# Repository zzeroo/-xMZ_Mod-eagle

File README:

# xMZ-Mod-Touch Eagle Files

Eagle files for the 'xMZ-Mod-Touch' project.

# Material Listen (BOM)

Die Material Listen werden aus den Eagle Zeichnungen gewonnen. Hierzu werden in 
Eagle zunächst über den "design link" alle Bauteile in der Farnell Datenbank 
gesucht.
Anschließend wird diese Liste gespeichert.

* Datei: "Deckelplatine $VERSION-order.txt"

Danach wird das bom.ulp in Eagle ausgeführt. Folgende Einstellungen sind zu
wählen:

	Listen-Typ: Werte (Häckchen unter "Attribute auflisten" setzen)
	Ausgabeformat: CSV
	
Diese Datei wird ebenfalls gespeichert.

* Datei: "Deckelplatine $VERSION BOM.csv"

### Farnell BOM Import

Farnell bietet die Möglichkeit über eine Web GUI die BOM Daten in eine 
Bestellung umzuwandeln.

Format der CSV Datei für den Import:
- 3 Spalten
"Anzahl	Ordercode	Beschreibung"
- Dateiformat .xls

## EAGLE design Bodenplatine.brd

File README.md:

# xMZ-Mod-Touch Eagle Files

Eagle files for the 'xMZ-Mod-Touch' project.

# Material Listen (BOM)

Die Material Listen werden aus den Eagle Zeichnungen gewonnen. Hierzu werden in
Eagle zunächst über den "design link" alle Bauteile in der Farnell Datenbank
gesucht.
Anschließend wird diese Liste gespeichert.

* Datei: "Deckelplatine $VERSION-order.txt"

Danach wird das bom.ulp in Eagle ausgeführt. Folgende Einstellungen sind zu
wählen:

	Listen-Typ: Werte (Häckchen unter "Attribute auflisten" setzen)
	Ausgabeformat: CSV

Diese Datei wird ebenfalls gespeichert.

* Datei: "Deckelplatine $VERSION BOM.csv"

### Farnell BOM Import

Farnell bietet die Möglichkeit über eine Web GUI die BOM Daten in eine
Bestellung umzuwandeln.

Format der CSV Datei für den Import:
- 3 Spalten
"Anzahl	Ordercode	Beschreibung"
- Dateiformat .xls

#Produktionsdaten
## Boardlayout Dateien

Einige der wichtigsten Ebenen (Drill, Solder, Paste) wurden einzeln mit der
Document (Layer 48) Ebene als PDF gedruckt

gs -dBATCH -dNOPAUSE -q -sDEVICE=pdfwrite -sOutputFile=Bodenplatine.pdf \
"Bodenplatine Dimensions.pdf" \
"Bodenplatine Placement TOP.pdf" \
"Bodenplatine PCB: TOP Layer.pdf" \
"Bodenplatine PCB: BOTTOM Layer.pdf" \
"Bodenplatine TOP Paste.pdf" \
"Bodenplatine TOP Solder Mask.pdf" \
"Bodenplatine Drill Drawing.pdf"

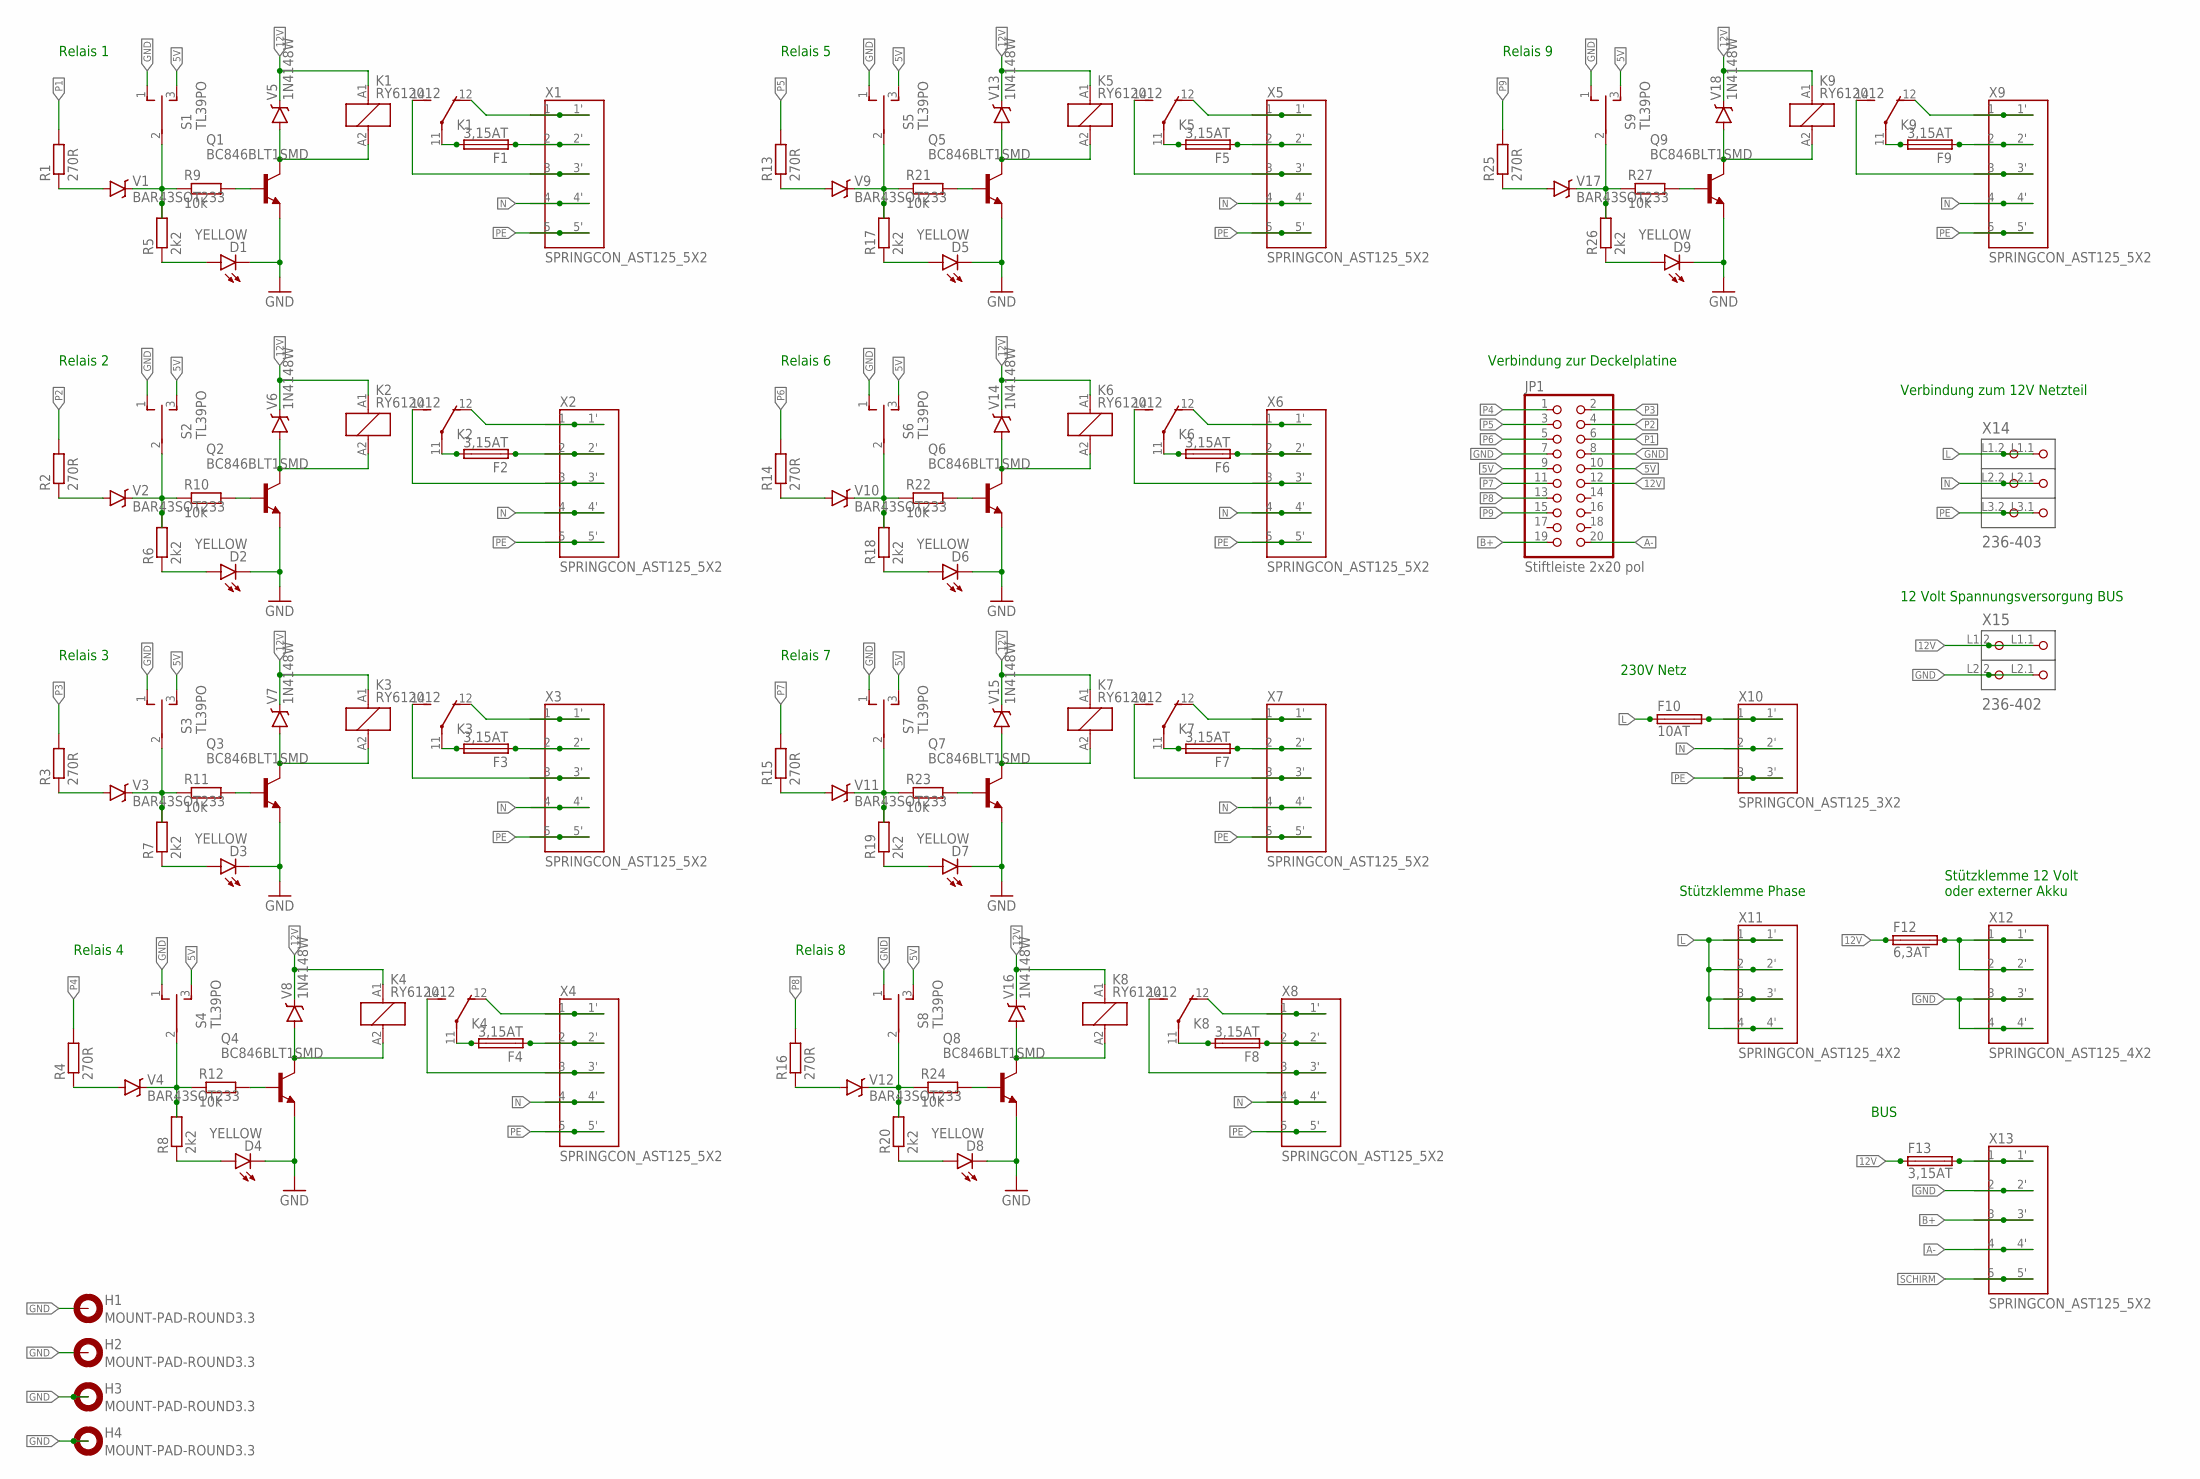
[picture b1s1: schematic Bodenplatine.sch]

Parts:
D1, D2, D3, D4, D5, D6, D7, D8, D9: YELLOW; LED-1206; MPN KP-3216SYC
F1, F2, F3, F4, F5, F6, F7, F8, F9, F13: 3,15AT; FPG4
F10: 10AT; FPG4
F12: 6,3AT; FPG4
H1, H2, H3, H4: MOUNT-PAD-ROUND3.3; 3,3-PAD
JP1: Stiftleiste 2x20 pol; 2X10; MPN 825440-5
K1, K2, K3, K4, K5, K6, K7, K8, K9: RY612012; RY-II; MPN V23061B1005A301
Q1, Q2, Q3, Q4, Q5, Q6, Q7, Q8, Q9: BC846BLT1SMD; SOT23; MPN BC846BWT1G
R1, R2, R3, R4, R13, R14, R15, R16, R25: 270R; M0805; MPN MC01W08055270R
R5, R6, R7, R8, R17, R18, R19, R20, R26: 2k2; R0603; MPN MC0063W060352K2
R9, R10, R11, R12, R21, R22, R23, R24, R27: 10k; R0603; MPN CPF0603B10KE1
S1, S2, S3, S4, S5, S6, S7, S8, S9: TL39PO; TL3XPO; MPN A103SYCQ04
V1, V2, V3, V4, V9, V10, V11, V12, V17: BAR43SOT233; SOT23; MPN BAR43
V5, V6, V7, V8, V13, V14, V15, V16, V18: 1N4148W; MINIMELF; MPN LL4148-GS08
X1, X2, X3, X4, X5, X6, X7, X8, X9, X13: SPRINGCON_AST125_5X2
X10: SPRINGCON_AST125_3X2
X11, X12: SPRINGCON_AST125_4X2
X14: 236-403; P-236-403; MPN 236-403
X15: 236-402; P-236-402; MPN 236-402

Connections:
5V: JP1.9, JP1.10, S1.3 (S), S2.3 (S), S3.3 (S), S4.3 (S), S5.3 (S), S6.3 (S), S7.3 (S), S8.3 (S), S9.3 (S)
12V: F12.1, F12.1' (1), F13.1, F13.1' (1), JP1.12, K1.A1 (1), K2.A1 (1), K3.A1 (1), K4.A1 (1), K5.A1 (1), K6.A1 (1), K7.A1 (1), K8.A1 (1), K9.A1 (1), V5.C, V6.C, V7.C, V8.C, V13.C, V14.C, V15.C, V16.C, V18.C, X15.L1.1 (P1.1), X15.L1.2 (P1.2)
A-: JP1.20, X13.4, X13.4' (4)
B+: JP1.19, X13.3, X13.3' (3)
GND: D1.C, D2.C, D3.C, D4.C, D5.C, D6.C, D7.C, D8.C, D9.C, H1.B3,3, H2.B3,3, H3.B3,3, H4.B3,3, JP1.7, JP1.8, Q1.2 (E), Q2.2 (E), Q3.2 (E), Q4.2 (E), Q5.2 (E), Q6.2 (E), Q7.2 (E), Q8.2 (E), Q9.2 (E), S1.1 (O), S2.1 (O), S3.1 (O), S4.1 (O), S5.1 (O), S6.1 (O), S7.1 (O), S8.1 (O), S9.1 (O), X12.3, X12.3' (3), X12.4, X12.4' (4), X13.2, X13.2' (2), X15.L2.1 (P2.1), X15.L2.2 (P2.2)
L: F10.1, F10.1' (1), X11.1, X11.1' (1), X11.2, X11.2' (2), X11.3, X11.3' (3), X11.4, X11.4' (4), X14.L1.1 (P1.1), X14.L1.2 (P1.2)
N: X1.4, X1.4' (4), X2.4, X2.4' (4), X3.4, X3.4' (4), X4.4, X4.4' (4), X5.4, X5.4' (4), X6.4, X6.4' (4), X7.4, X7.4' (4), X8.4, X8.4' (4), X9.4, X9.4' (4), X10.2, X10.2' (2), X14.L2.1 (P2.1), X14.L2.2 (P2.2)
unnamed: F2.1, F2.1' (1), X2.2, X2.2' (2)
unnamed: K2.14 (S), X2.3, X2.3' (3)
unnamed: F2.2, F2.2' (2), K2.11
unnamed: K2.12 (O), X2.1, X2.1' (1)
unnamed: K2.A2 (2), Q2.3 (C), V6.A
unnamed: K3.14 (S), X3.3, X3.3' (3)
unnamed: R2.1, V2.1 (A)
unnamed: R6.2, R10.1, S2.2, V2.3 (C)
unnamed: D2.A, R6.1
unnamed: Q2.1 (B), R10.2
unnamed: F3.2, F3.2' (2), K3.11
unnamed: R3.1, V3.1 (A)
unnamed: R7.2, R11.1, S3.2, V3.3 (C)
unnamed: D3.A, R7.1
unnamed: Q3.1 (B), R11.2
unnamed: K3.A2 (2), Q3.3 (C), V7.A
unnamed: F3.1, F3.1' (1), X3.2, X3.2' (2)
unnamed: K3.12 (O), X3.1, X3.1' (1)
unnamed: K4.14 (S), X4.3, X4.3' (3)
unnamed: F4.2, F4.2' (2), K4.11
unnamed: R4.1, V4.1 (A)
unnamed: R8.2, R12.1, S4.2, V4.3 (C)
unnamed: D4.A, R8.1
unnamed: Q4.1 (B), R12.2
unnamed: K4.A2 (2), Q4.3 (C), V8.A
unnamed: F4.1, F4.1' (1), X4.2, X4.2' (2)
unnamed: K4.12 (O), X4.1, X4.1' (1)
unnamed: K5.14 (S), X5.3, X5.3' (3)
unnamed: F5.2, F5.2' (2), K5.11
unnamed: R13.1, V9.1 (A)
unnamed: R17.2, R21.1, S5.2, V9.3 (C)
unnamed: D5.A, R17.1
unnamed: Q5.1 (B), R21.2
unnamed: K5.A2 (2), Q5.3 (C), V13.A
unnamed: F5.1, F5.1' (1), X5.2, X5.2' (2)
unnamed: K5.12 (O), X5.1, X5.1' (1)
unnamed: K6.14 (S), X6.3, X6.3' (3)
unnamed: F6.2, F6.2' (2), K6.11
unnamed: R14.1, V10.1 (A)
unnamed: R18.2, R22.1, S6.2, V10.3 (C)
unnamed: D6.A, R18.1
unnamed: Q6.1 (B), R22.2
unnamed: K6.A2 (2), Q6.3 (C), V14.A
unnamed: F6.1, F6.1' (1), X6.2, X6.2' (2)
unnamed: K6.12 (O), X6.1, X6.1' (1)
unnamed: K7.14 (S), X7.3, X7.3' (3)
unnamed: F7.2, F7.2' (2), K7.11
unnamed: R15.1, V11.1 (A)
unnamed: R19.2, R23.1, S7.2, V11.3 (C)
unnamed: D7.A, R19.1
unnamed: Q7.1 (B), R23.2
unnamed: K7.A2 (2), Q7.3 (C), V15.A
unnamed: F7.1, F7.1' (1), X7.2, X7.2' (2)
unnamed: K7.12 (O), X7.1, X7.1' (1)
unnamed: K8.14 (S), X8.3, X8.3' (3)
unnamed: F8.2, F8.2' (2), K8.11
unnamed: R16.1, V12.1 (A)
unnamed: R20.2, R24.1, S8.2, V12.3 (C)
unnamed: D8.A, R20.1
unnamed: Q8.1 (B), R24.2
unnamed: K8.A2 (2), Q8.3 (C), V16.A
unnamed: F8.1, F8.1' (1), X8.2, X8.2' (2)
unnamed: K8.12 (O), X8.1, X8.1' (1)
unnamed: K9.14 (S), X9.3, X9.3' (3)
unnamed: F9.2, F9.2' (2), K9.11
unnamed: R25.1, V17.1 (A)
unnamed: R26.2, R27.1, S9.2, V17.3 (C)
unnamed: D9.A, R26.1
unnamed: Q9.1 (B), R27.2
unnamed: K9.A2 (2), Q9.3 (C), V18.A
unnamed: F9.1, F9.1' (1), X9.2, X9.2' (2)
unnamed: K9.12 (O), X9.1, X9.1' (1)
unnamed: K1.14 (S), X1.3, X1.3' (3)
unnamed: F1.2, F1.2' (2), K1.11
unnamed: R1.1, V1.1 (A)
unnamed: R5.2, R9.1, S1.2, V1.3 (C)
unnamed: D1.A, R5.1
unnamed: Q1.1 (B), R9.2
unnamed: K1.A2 (2), Q1.3 (C), V5.A
unnamed: F1.1, F1.1' (1), X1.2, X1.2' (2)
unnamed: K1.12 (O), X1.1, X1.1' (1)
unnamed: F10.2, F10.2' (2), X10.1, X10.1' (1)
unnamed: F13.2, F13.2' (2), X13.1, X13.1' (1)
unnamed: F12.2, F12.2' (2), X12.1, X12.1' (1), X12.2, X12.2' (2)
P1: JP1.6, R1.2
P2: JP1.4, R2.2
P3: JP1.2, R3.2
P4: JP1.1, R4.2
P5: JP1.3, R13.2
P6: JP1.5, R14.2
P7: JP1.11, R15.2
P8: JP1.13, R16.2
P9: JP1.15, R25.2
PE: X1.5, X1.5' (5), X2.5, X2.5' (5), X3.5, X3.5' (5), X4.5, X4.5' (5), X5.5, X5.5' (5), X6.5, X6.5' (5), X7.5, X7.5' (5), X8.5, X8.5' (5), X9.5, X9.5' (5), X10.3, X10.3' (3), X14.L3.1 (P3.1), X14.L3.2 (P3.2)
SCHIRM: X13.5, X13.5' (5)

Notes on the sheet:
Relais 2
Relais 3
Relais 4
Relais 5
Relais 6
Relais 7
Relais 8
Relais 9
Relais 1
Verbindung zur Deckelplatine
230V Netz
Stützklemme Phase
Stützklemme 12 Volt oder externer Akku
BUS
Verbindung zum 12V Netzteil
12 Volt Spannungsversorgung BUS

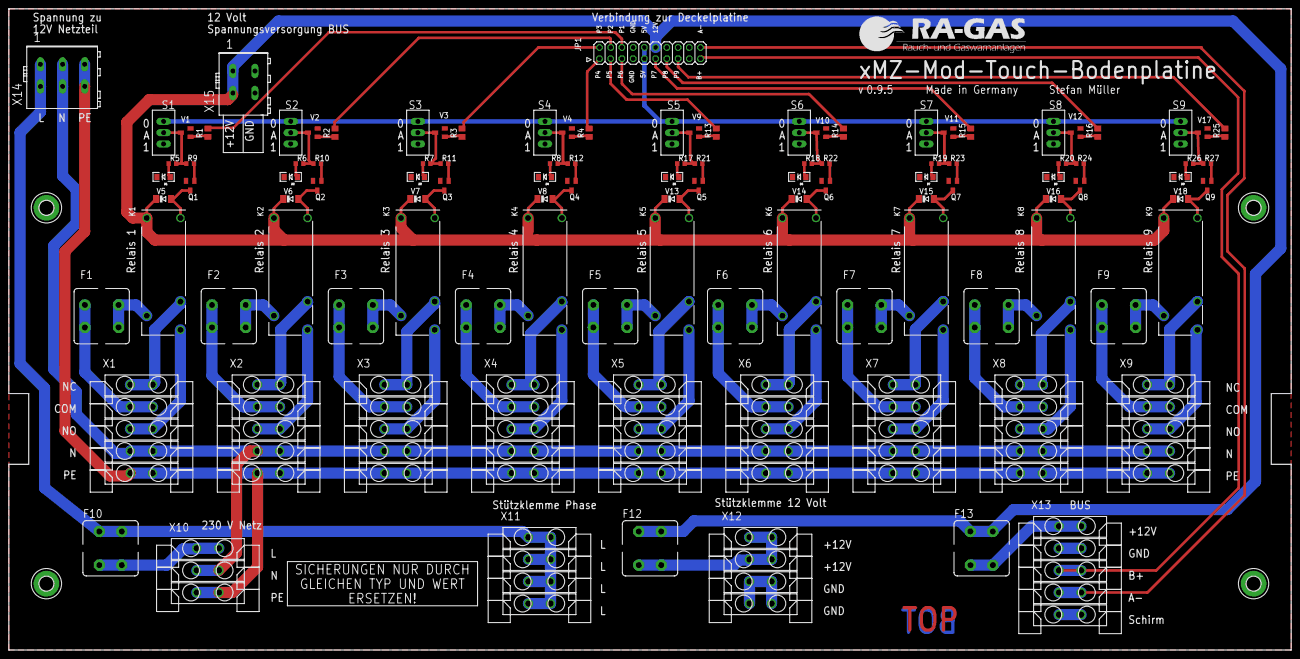
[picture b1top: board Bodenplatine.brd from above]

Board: 2 copper layers, 290.0 x 145.0 mm, 118 parts (0 on the bottom side), 102 nets.

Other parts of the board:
DRILEGEND: DRILEGEND
U$1: TEXT_FUSE
U$2: TEXT_NAME_VERSION_AUTHOR
U$3: LOGO_RA-GAS
U$5: A3-LOC-RA-GAS

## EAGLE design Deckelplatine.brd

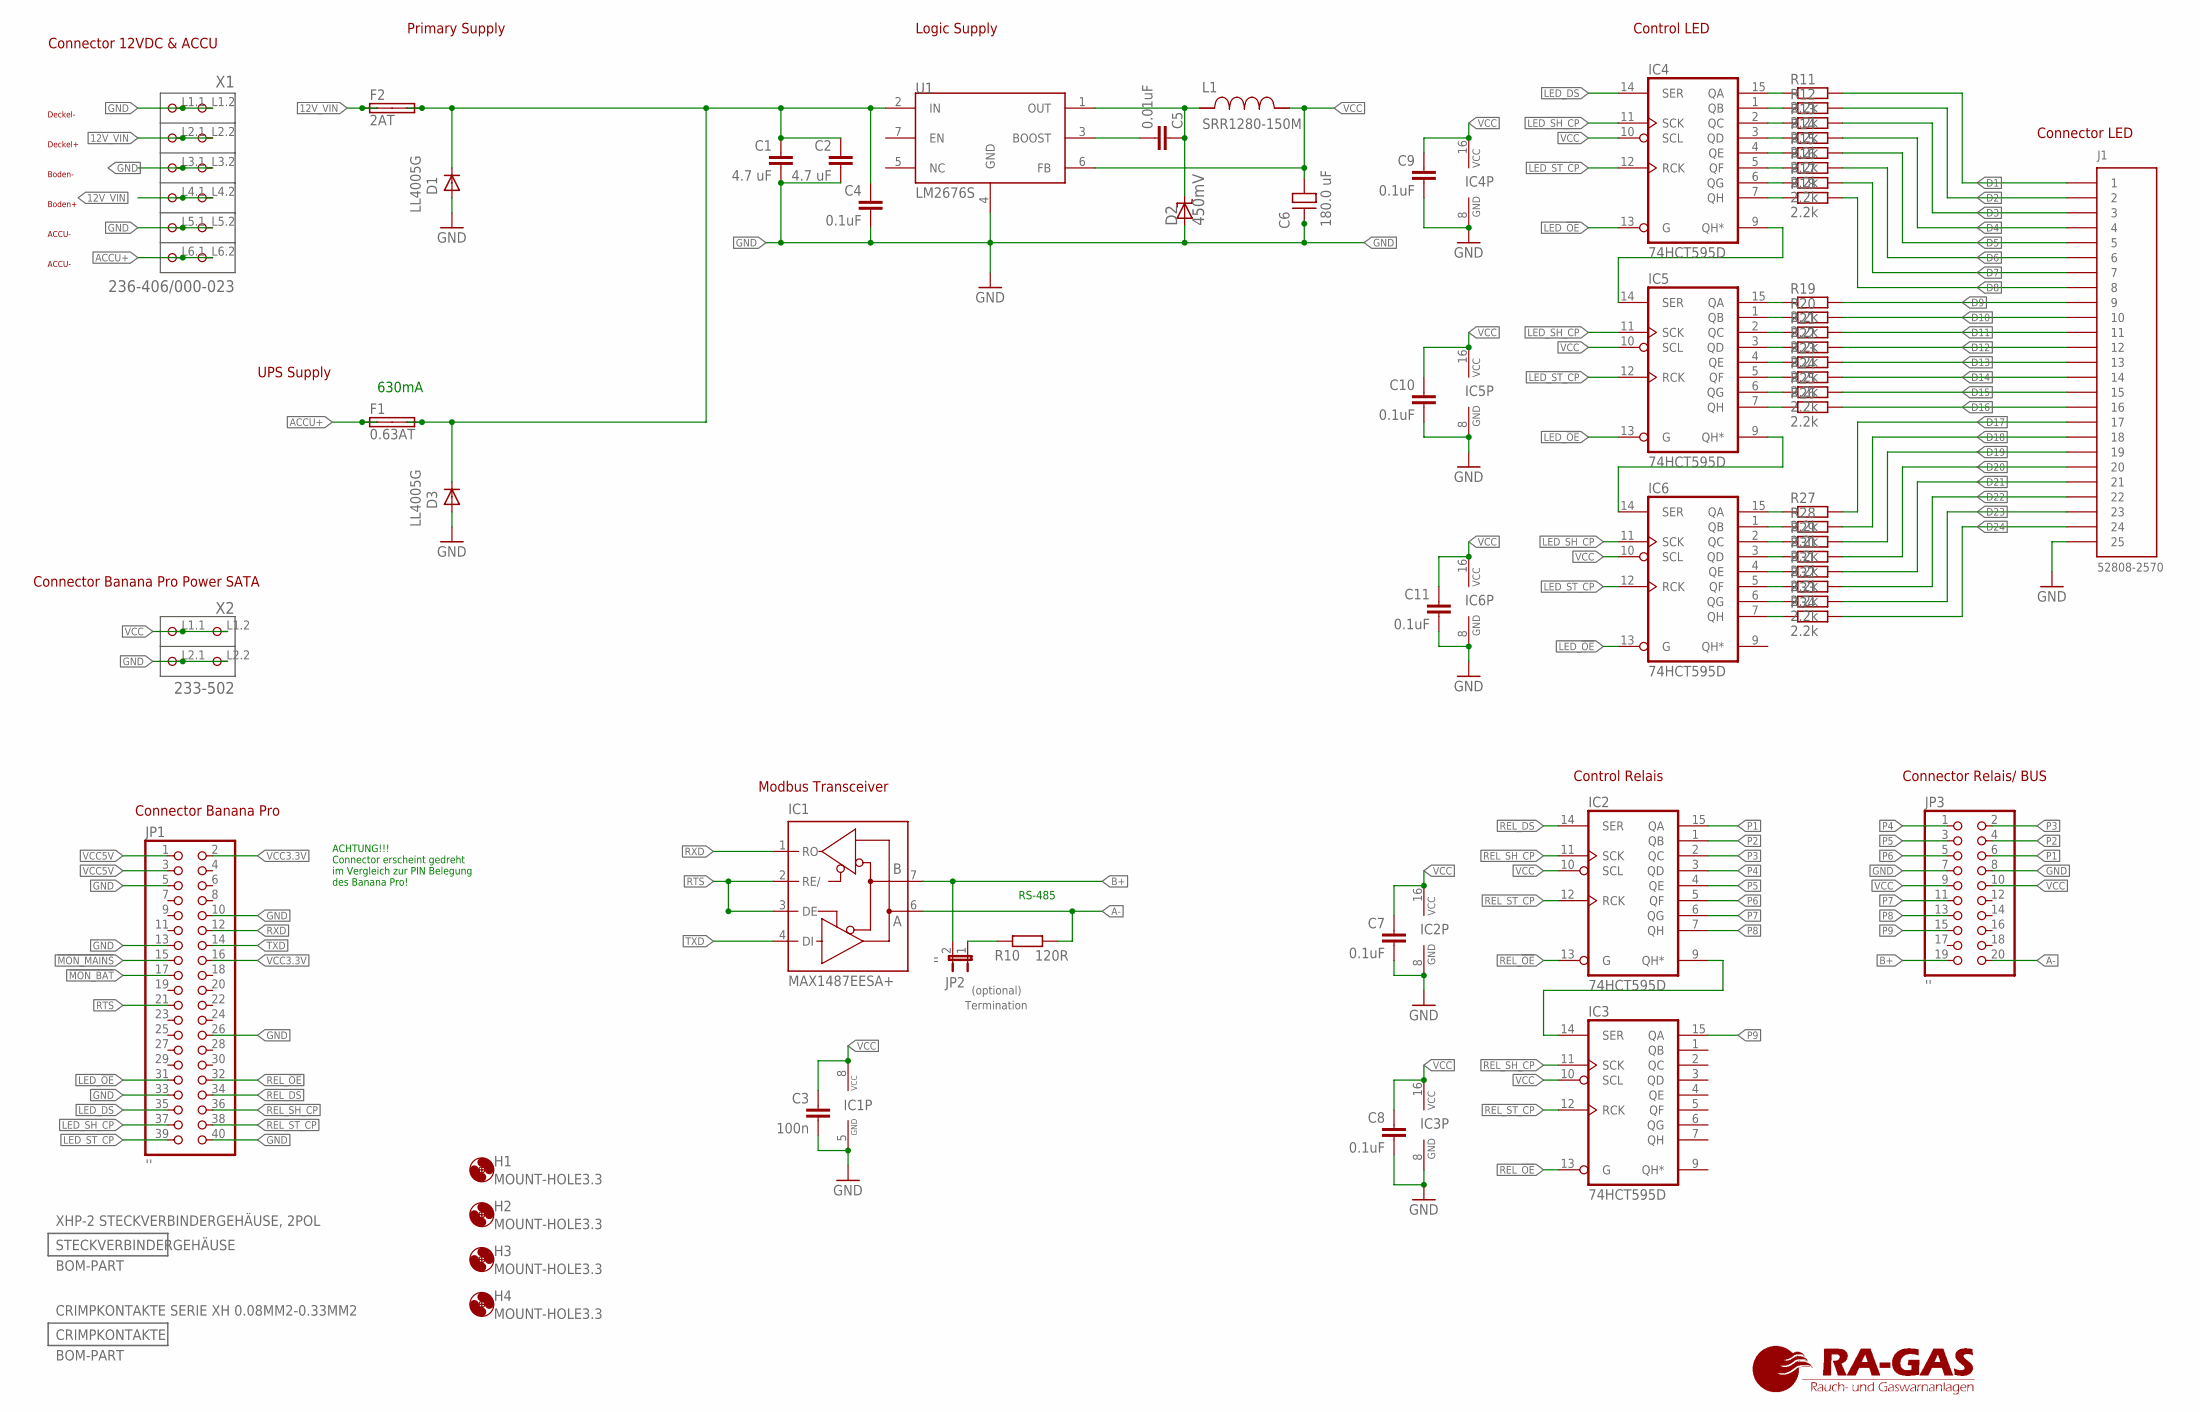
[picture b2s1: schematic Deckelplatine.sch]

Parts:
C1, C2: 4.7 uF; GRM21BR61E475MA12L; MPN GRM21BR61E475MA12L
C3: 100n; C0603; MPN C0603C104K8RACTU
C4: 0.1uF; 0805; MPN 08053C104KAT2A
C5: 0.01uF; GRM216R71H103KA01D; MPN GRM216R71H103KA01D
C6: 180.0 uF; SM_RADIAL_10MM; MPN 16SVP180MX
C7, C8, C9, C10, C11: 0.1uF; C0603; MPN C0603C104K8RACTU
D1, D3: LL4005G; MELF-MLL41; MPN LL4005G
D2: 450mV; SMB; MPN B340LB-13-F
F1: 0.63AT; 01110005MR; MPN 01110005MR
F2: 2AT; 01110005MR; MPN 01110005MR
H1, H2, H3, H4: MOUNT-HOLE3.3; 3,3
IC1: MAX1487EESA+; SO08; MPN MAX1487EESA+
IC2, IC3, IC4, IC5, IC6: 74HCT595D; SO16; MPN 74HCT595D
J1: 52808-2570; MPN 52808-2570
JP1: ''; 2X20; MPN M20-6112045
JP2: ''; JP1; MPN 825433-2
JP3: ''; 2X10; MPN 5103308-5
L1: SRR1280-150M; SRR1280; MPN MSS1278-153MLD
R10: 120R; R1206; MPN CRGH1206F120R
R11, R12, R13, R14, R15, R16, R17, R18, R19, R20, R21, R22, R23, R24, R25, R26, R27, R28, R29, R30, R31, R32, R33, R34: 2.2k; R0603; MPN RC0603FR-072K2L
U1: LM2676S; TO-263-7; MPN LM2676S-5.0/NOPB
X1: 236-406/000-023; P-236-406; MPN 236-406
X2: 233-502; P-233-502; MPN 233-502.

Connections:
12V_VIN: F2.1A, F2.1B, X1.L2.1 (P2.1), X1.L2.2 (P2.2), X1.L4.1 (P4.1), X1.L4.2 (P4.2)
!MON_BAT: JP1.17
!MON_MAINS: JP1.15
A-: IC1.6 (A), JP3.20, R10.2
ACCU+: F1.1A, F1.1B, X1.L6.1 (P6.1), X1.L6.2 (P6.2)
B+: IC1.7 (B), JP2.2, JP3.19
D1: J1.1, R11.2
D2: J1.2, R12.2
D3: J1.3, R13.2
D4: J1.4, R14.2
D5: J1.5, R15.2
D6: J1.6, R16.2
D7: J1.7, R17.2
D8: J1.8, R18.2
D9: J1.9, R19.2
D10: J1.10, R20.2
D11: J1.11, R21.2
D12: J1.12, R22.2
D13: J1.13, R23.2
D14: J1.14, R24.2
D15: J1.15, R25.2
D16: J1.16, R26.2
D17: J1.17, R27.2
D18: J1.18, R28.2
D19: J1.19, R29.2
D20: J1.20, R30.2
D21: J1.21, R31.2
D22: J1.22, R32.2
D23: J1.23, R33.2
D24: J1.24, R34.2
GND: C1.2, C2.2, C3.2, C4.2, C6.2 (-), C7.2, C8.2, C9.2, C10.2, C11.2, D1.A, D2.A, D3.A, IC1.5 (GND), IC2.8 (GND), IC3.8 (GND), IC4.8 (GND), IC5.8 (GND), IC6.8 (GND), J1.25, JP1.5, JP1.10, JP1.13, JP1.26, JP1.33, JP1.40, JP3.7, JP3.8, U1.4 (GND), X1.L1.1 (P1.1), X1.L1.2 (P1.2), X1.L3.1 (P3.1), X1.L3.2 (P3.2), X1.L5.1 (P5.1), X1.L5.2 (P5.2), X2.L2.1 (P2.1), X2.L2.2 (P2.2)
LED_!OE: IC4.13 (G), IC5.13 (G), IC6.13 (G), JP1.31
LED_DS: IC4.14 (SER), JP1.35
LED_SH_CP: IC4.11 (SCK), IC5.11 (SCK), IC6.11 (SCK), JP1.37
LED_ST_CP: IC4.12 (RCK), IC5.12 (RCK), IC6.12 (RCK), JP1.39
unnamed: IC5.9 (QH*), IC6.14 (SER)
unnamed: IC2.9 (QH*), IC3.14 (SER)
unnamed: C1.1, C2.1, C4.1, D1.C, D3.C, F1.2A, F1.2B, F2.2A, F2.2B, U1.2 (IN)
unnamed: IC4.9 (QH*), IC5.14 (SER)
unnamed: IC4.15 (QA), R11.1
unnamed: IC4.1 (QB), R12.1
unnamed: IC4.2 (QC), R13.1
unnamed: IC4.3 (QD), R14.1
unnamed: IC4.4 (QE), R15.1
unnamed: IC4.5 (QF), R16.1
unnamed: IC4.6 (QG), R17.1
unnamed: IC4.7 (QH), R18.1
unnamed: IC5.15 (QA), R19.1
unnamed: IC5.1 (QB), R20.1
unnamed: IC5.2 (QC), R21.1
unnamed: IC5.3 (QD), R22.1
unnamed: JP2.1, R10.1
unnamed: IC5.4 (QE), R23.1
unnamed: IC5.5 (QF), R24.1
unnamed: IC5.6 (QG), R25.1
unnamed: IC5.7 (QH), R26.1
unnamed: IC6.15 (QA), R27.1
unnamed: IC6.1 (QB), R28.1
unnamed: IC6.2 (QC), R29.1
unnamed: IC6.3 (QD), R30.1
unnamed: IC6.4 (QE), R31.1
unnamed: IC6.5 (QF), R32.1
unnamed: IC6.6 (QG), R33.1
unnamed: IC6.7 (QH), R34.1
unnamed: C5.2, U1.3 (BOOST)
unnamed: C5.1, D2.C, L1.1, U1.1 (OUT)
P1: IC2.15 (QA), JP3.6
P2: IC2.1 (QB), JP3.4
P3: IC2.2 (QC), JP3.2
P4: IC2.3 (QD), JP3.1
P5: IC2.4 (QE), JP3.3
P6: IC2.5 (QF), JP3.5
P7: IC2.6 (QG), JP3.11
P8: IC2.7 (QH), JP3.13
P9: IC3.15 (QA), JP3.15
REL_!OE: IC2.13 (G), IC3.13 (G), JP1.32
REL_DS: IC2.14 (SER), JP1.34
REL_SH_CP: IC2.11 (SCK), IC3.11 (SCK), JP1.36
REL_ST_CP: IC2.12 (RCK), IC3.12 (RCK), JP1.38
RTS: IC1.2 (RE/), IC1.3 (DE), JP1.21
RXD: IC1.1 (RO), JP1.12
TXD: IC1.4 (DI), JP1.14
VCC: C3.1, C6.1 (+), C7.1, C8.1, C9.1, C10.1, C11.1, IC1.8 (VCC), IC2.10 (SCL), IC2.16 (VCC), IC3.10 (SCL), IC3.16 (VCC), IC4.10 (SCL), IC4.16 (VCC), IC5.10 (SCL), IC5.16 (VCC), IC6.10 (SCL), IC6.16 (VCC), JP3.9, JP3.10, L1.2, U1.6 (FB), X2.L1.1 (P1.1), X2.L1.2 (P1.2)
VCC3.3V: JP1.2, JP1.16
VCC5V: JP1.1, JP1.3

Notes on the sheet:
Connector Relais/ BUS
Connector Banana Pro
RS-485
Termination
(optional)
Modbus Transceiver
Connector LED
Control LED
Control Relais
Connector 12VDC & ACCU
UPS Supply
Primary Supply
Logic Supply
Connector Banana Pro Power SATA
630mA
ACCU-
ACHTUNG!!! Connector erscheint gedreht im Vergleich zur PIN Belegung des Banana Pro!
Boden-
Boden+
Deckel-
Deckel+

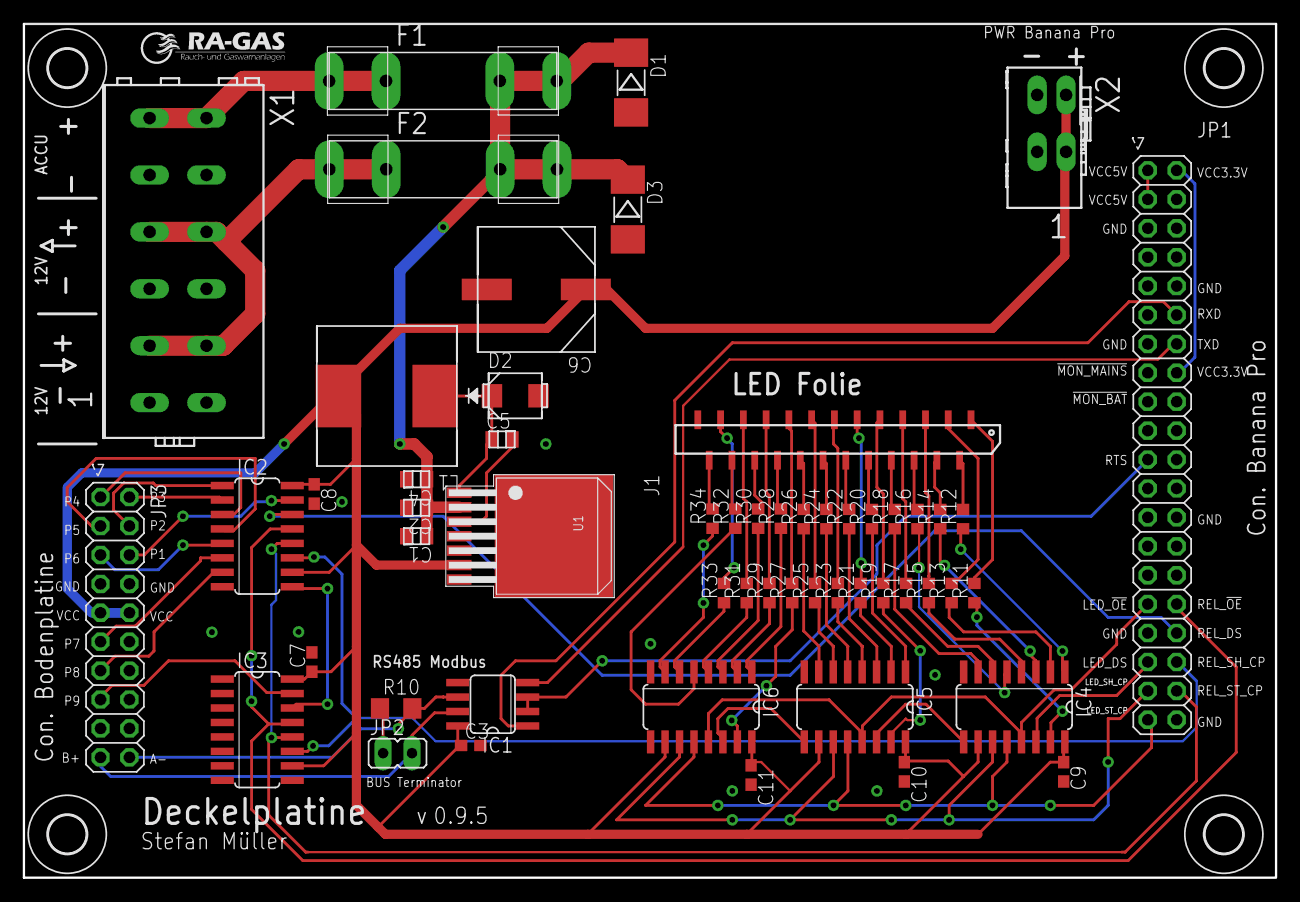
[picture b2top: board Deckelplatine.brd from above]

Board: 2 copper layers, 110.0 x 75.0 mm, 61 parts (0 on the bottom side), 83 nets.

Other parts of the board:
U$2: LOGO_RA-GAS-SMALL
U$3: TEXT_NAME_VERSION_AUTHOR-SMALL

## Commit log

2015-05-22 Erste Version der Eagle Projekt Dateien für xMZ_Mod
    Auf diesem Stand wurde heute, bei Farnell das Material für
    2 Bestückungen bestellt.
    Das PCB Board Design wird mit den Bauteilen zusammen durchgeführt.
2015-05-27 Begin mit dem Board Layout
    Erste Lieferung von Farnell angekommen.
2015-05-28 Stromlaufplan fast fertig.
2015-06-01 Schema mit Verpolschutz an Vin und Accu.
    Schaltregler nach Application Note von Texas Instruments.
    Eingänge für den MON_MAINS und MON_BAT (GPIO Banana Pro Eingänge zur Überwachung Vin und Accu) sind durch NPN Transistoren gegen Überspannunge geschützt
2015-06-01 Widerstand 150Ohm, 4Watt ausgetauscht
2015-06-02 Schema, Board Layout und Routing komplett
2015-06-02 Autorouter mit 7 Airwire left
2015-06-03 Routing fertig, keine Airwires übrig
2015-06-03 Erste ferige Version nach Tausch der Sicherung
    Board Layout, Schema, dicke Power Lines, neue Sicherung
2015-06-05 Schaltregler überarbeitet, Teil 1
    CIN angepasst, Größe stimmte nicht (zu klein).
    Materialliste Farnell an Schaltplan "webench_design_4385517_7_60043841.pdf" angepasst.
2015-06-05 Nach 2. Bestellung bei Farnell
    Schaltregler Induktion musste nochmals ausgewechselt werden da
    die vorherige nur aus USA importierbar wäre.
2015-06-09 Readme aktualisiert
2015-06-19 Datasheet Shift Register
2015-07-02 Erste Version in der PCB Produktion (Conrad)
    Dies ist die erste Produktion die über https://www.leiterplattenservice.com/
    abgewickelt wurde.
    https://www.leiterplattenservice.com/code/my_orderhistory_details.html?nr=CR558950f00063a
    Details:
    -------
    Nachfolgend sehen Sie die Details der gewählten Bestellung CR558950f00063a. Die Bestellung erfolgte am 23.06.2015, 14:28:32.
2015-07-07 Zwischen Commit Änderungen leider nicht mehr klar
    Leider habe ich vergessen welche Änderungen dieser Commit mit sich brachte.
    Desshalb sollte dieser komplett ignoriert werden.
2015-07-07 Beta Version (v.0.9.1) begonnen
    Die Alpha Version (v.0.9.0) wurde produziert und bestückt.
    Erste Funktionstests waren alle erfolgreich.
    Somit beginnt mit diesem Commit nun die Beta Phase der
    Hardware Entwicklung.
    In diesem Commit sind viele (nicht alle) Datenblätter für die
    Komponenten der Hardware zu finden.
2016-01-20 Connector Banana Pro Power SATA verschoben
2016-01-20 Erste Version der Deckelplatine
2016-01-20 Erste Version der Projekt eigenen Eagle Library
    Alle Parts sollen von nun an für jedes Projekt in eine seperate Eagle lbr Datei gepackt werden. Nur Teile aus dieser Library sollen verwendet werden.
    Das geschieht um einen besseren Überblick über die verwendeten Teile zu erhalten. Außerdem kann die Eagle Zeichnung incl. der Parts weiter gegeben werden.
2016-01-21 Exclude lbr backup files
2016-01-21 Erste Version des 'RIACON AST125 1x2'
2016-01-23 Alle Connectoren auf 0.01 inch Raster neu gezeichnet.
2016-01-25 Bessere Footprints und Pin Bezeichnung.
2016-01-25 Erste fast fertige Version des Schaltplans der Bodebplatine
    Es fehlt nur noch die Wago Klemme für L/N/PE Netzteil und 12V+/-
2016-01-25 Einige Datenblätter hinzugefügt
2016-01-26 Begin mit dem Bord der Bodenplatine
    Schriften in den Schaltplänen einheitlich gemacht (Layer und Große)
2016-01-26 Relais neu sortiert (umbenannt)
2016-01-26 Tiny Switches über den Relais vergessen
2016-01-26 BC486 ausgetauscht
2016-01-26 Korrektur zum letzten Commit, Ein BC486 vergessen
2016-01-26 Alle Bauteile auf dem Board, teilweise genau positioniert.
    GND ground plane auf beiden Seiten
2016-01-26 Alle Connectoren mit 2 Pins richtig verbunden.@
2016-01-26 Doppelte Kontakte der Connectoren verbunden
2016-01-26 PL FPG4-40 :: Sicherungshalter, 5x20mm, max. 10A-250V
    www.reichelt.de/PL-FPG4-40/3/index.html?&ACTION=3&LA=446&artnr=PL+FPG4-40&SEARCH=PL+FPG+4-40
2016-01-26 Sicherungshalter nach FPG4 ausgetauscht
2016-01-27 >NAME und >VALUE den Springcon Packages hinzugefügt
2016-01-27 Relais Anschlüsse A1 und A2 im Schema gedreht
2016-01-27 Neue VISHAY LL4148 Diode
2016-01-27 Replace LL4148 Diode
2016-01-27 Datasheet für die LL4148 Diode
2016-01-27 BAR43 Kleinsignal Schottky Diode hinzugefügt
2016-01-27 BAR43 Diode verbaut und eingebunden
2016-01-27 Hupe sollte auf der Deckelplatine zum Einsatz kommen
2016-01-27 Dioden, Relais und mini Toggle Switch mit Daten von Farnell gefüttert
2016-01-27 BOM und xlsx Datei für den Warenkorb import Farnell
    Die txt Datei wurde aus Eagle mit 'design link' exportiert
    Daraus dann mit LibreOffice eine xslx Datei generiert.
2016-01-27 Prefix für die Sicherungen FPG4 gesetzt (F)
2016-01-27 Prefix übernommen und GND plane im Board layout benannt
2016-01-27 Leucht Dioden ausgerichtet
2016-01-27 NPN Transistoren ausgerichtet
2016-01-27 Relais neu sortiert 1...9
2016-01-27 Vertauschte Dioden gefixt
2016-01-27 Widerstände und Dioden ausgerichtet
2016-01-27 Import der Wago Klemmen in die Bibliothek
2016-01-27 Begin Änderungen der Klemmenbezeichnungen
2016-01-27 Erste finale Version OHNE CHECKS
2016-01-28 Cleanup alle Sicherheitskopien entfernt
2016-01-28 Alle Datasheets der Bodenplatine vorhanden
    Auserdem noch einige Änderungen an den Footprints der Bodenplatine
2016-01-28 Logos auf dem Board und Außenmaße mit Kerben
2016-01-28 Eagle Logo Script für das RA-GAS Logo
2016-01-28 Logos auch auf Schaltplan X und K Bezeichnungen auf Board verbessert
2016-01-29 Schaltplan Bodenplaine
2016-01-29 Neu versioniert, Finale Bodenplatte BETA Version
2016-01-30 Readme umbenannt
2016-01-30 Remove sinnloses zip backup file. Git ist mein backup
2016-02-04 Logo Script für kleinere Version
2016-02-08 Logo RA-GAS small hinzugefügt
2016-02-08 Dateinamen umbenannt, die Versionsnummer wird in Git geführt
2016-02-09 Schmalere Version des Fuse Textes
2016-02-09 Little Fuses Datasheet (evtl. falsch)
2016-02-09 Ein wenig Kosmetik auf der Deckelplatine
    Beschriftungen angepasst
2016-02-09 Cleanup
2016-02-09 TODO Liste angelegt
2016-02-17 Versionsnummer aus Dateinamen entfernt
    Git kann Versionsnummern viel besser verwalten.
    Ausserdem wurden ettliche 'alte' Dateien gelöscht. Sollten diese je wieder gebraucht werden dann kann der Git tag v0.9.0 ausgecheckt werden.
    Ä
2016-02-17 Fix 12V Spannungsversorgung vergessen ><
2016-02-19 Kosmetische Verbesserungen
2016-02-19 Konvert via Eagle2KiCAD scripts
2016-02-19 Von eagle2kicad erstelles script vergessen
2016-02-23 Logo RA-GAS nun hoffentlich ohne Stoplack
2016-02-23 A3 Rahmen mit RA-GAS Logo versehen
2016-02-23 Neues PACKAGE (für .brd) A3 Rahmen mit RA-GAS Logo
2016-02-23 >DESCRIPTION Attribut eingefügt
2016-02-23 A3 Rahmen in BRD eingefügt
2016-02-23 Dimensionen hinzugefügt
2016-02-23 Dateum für PCB Rahmen A3 angepasst.
2016-02-23 Produktionsdaten PDF Drucke fertig gemacht
2016-02-23 TOP und BOTTOM in Kupfer aufgebracht, so das keine Verwechslungen der Layer auftreten können
2016-02-23 Eagle design rules für multi-circut-boards.eu
    http://www.multi-circuit-boards.eu/support/leiterplatten-daten/eagle.html
2016-02-23 Produktionsdaten neu sortiert
2016-02-23 Finale Version, zu Multi-CB hochgeladen
2016-02-23 Schaltplan als PDF noch hinzugekommen

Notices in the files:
parts and their libraries:
bom: Copyright (C) 2010, Bob Starr
